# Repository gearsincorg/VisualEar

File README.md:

Visual Ear project
By Phil Malone
Phil.Malone@Mr-Phil.com
6/21/2021

https://hackaday.io/project/175944-the-visual-ear 
 
 This project is an experiment in audio perception.
 My goal was to produce a visual display that might help a deaf person experience sound.
 I got excited when I imagined what an orchestral performance might look like if each musician had such a display above their head.
 
 I started thinking about this project when I discovered that our Cochlea (the sensing part of our inner ear) does not just contain "hairs" that turn vibrations into electrical signals. 
 Instead, it is comprised of many micro structures (containing hairs) which are located along a tapered structure that filters out increasing frequencies of sound as you move into the structure.
 So, in reality, each successive cluster of hairs is detecting higher frequency components. 
 
 Thus the Cochlea does not convert vibrations into electrical impulses, but instead, it converts audio frequencies into electrical impulses.  It's acting as a spectrum analyzer.
 This is a marvelous piece of evolutionary adaption which removed the requirement of the brain to sense signals that were changing many thousands of times a second.
 
 This was quite a revelation to me, and it made me wonder if an external device that converted sound waves into similar frequency bands, and then displayed these bands using light (color and intensity) could be a crude substitute for a Cochlea.

 My first instinct was to think of a spectrum analyzer display that you might see on a high-end audio amplifier.
 There is nothing new about visual audio-spectrum displays, but I decided that it would be important to provide MUCH finer spectral resolution, while still maintaining near real-time response.

Display Specs:

- Display Bands:  104 Bands, spanning 43 Hz - 16744 Hz (8.5 Octaves, 12 LED's per octave)
- Intensity Range: Each Band is displayed with a secific color, and 255 intensity levels
- Display Update interval: 11.6 mSec (86 Hz)
- Audio to Visual Latency:  Max 13.5 mSec (11.6 mSec acquisition + 1.9 mSec for dual FFT & display)
- Visual Persistance:  Low Frequency (< 440 Hz) 185 mSec.  High Frequency (>= 440 Hz) 46 mSec.

 ** HOW IT WORKS 
 
 Note:  Program constants are referenced in this description as follows:  64 (CONSTANT_NAME)
 
 The Teensy audio library is used to sample the I2S digital microphone continuously at the standard 44100 Hz rate.  Successive Bursts of 128 samples are cataloged and saved as an array of Burst pointers.  This array holds 72 (NUM_BURSTS) Burst pointers.  Only 64 (BURSTS_PER_AUDIO) of these are being processed at any time.  The remaining 8 (EXTRA_BURSTS) are used to start capturing more audio while the current Packet of 64 Bursts is processed.  
 
 To cover the full 55-17,153 Hz spectrum, its necessary to aquire 8192 samples (64 Bursts of 128 samples).  But this would take 185 mSec to collect, so its not practical to wait for the full sample to be collected before updating the display.  
 
 To permit faster display updates, a sliding window is created to process the most recent 64 Bursts, every time a new set of 4 (BURSTS_PER_FFT_UPDATE) Bursts have been received.  This event occurs every 11.6 mSec, which becomes the update rate for the overall display (86 updates per second).
 
 A standard FFT (Fast Fourier Transform) is used to convert the Audio Packet (8196 Samples) into frequency buckets.  Initially, a single FFT was used to process the entire sample.  This transform could be performed in the available 11.6 mSec, but a high frequency sound spike would be spread over the entire 185 mS sample duration.  So a sudden sound would appear quickly, but it would persist on the display for the full 185 mSec.  This effectively limits the responsiveness of the system to rapid sounds like a drum roll.
 
 To accommodate BOTH slow low-frequency sounds, and rapid high-frequency sounds, the available Audio packet is processed by two separate FFTs.  Each optimized for a different frequency range.  The Low FFT is looking for sounds in the 55-880 Hz range.   The High FFT is looking for sounds in the 880-17,153 Hz range.  
 
 To capture and resolve low sounds, the Low FFT uses the entire Audio Packet, but it only processes every fourth sample.  This enables the FFT to work with a smaller input sample set of 2048, which still produces 1024 frequency bins of 5.4Hz width.
 
 To capture and resolve rapid high sounds, the High-FFT only uses the most recent quarter of the Audio Packet, but at the full 44.1 kHz sample rate.  This enables this FFT to also work with a smaller input sample set of 2048, but produces 1024 frequency bins of 21.5Hz width.  Since this FFT is only using a quarter of the sample history, short-pulse sounds only persist for a max of 46.4 mSec, which should be able to display a 10 Hz drum-roll.
 
CREDITS:

 > A lot of what I developed here was influenced strongly by Steve Marley https://github.com/s-marley/ESP32_FFT_VU
 
 > An explanation of the Spreadsheet used to determine the Band Bins is found here: https://www.youtube.com/watch?v=Mgh2WblO5_c
 
 > This project adapts the FFT library found here : https://github.com/kosme/arduinoFFT

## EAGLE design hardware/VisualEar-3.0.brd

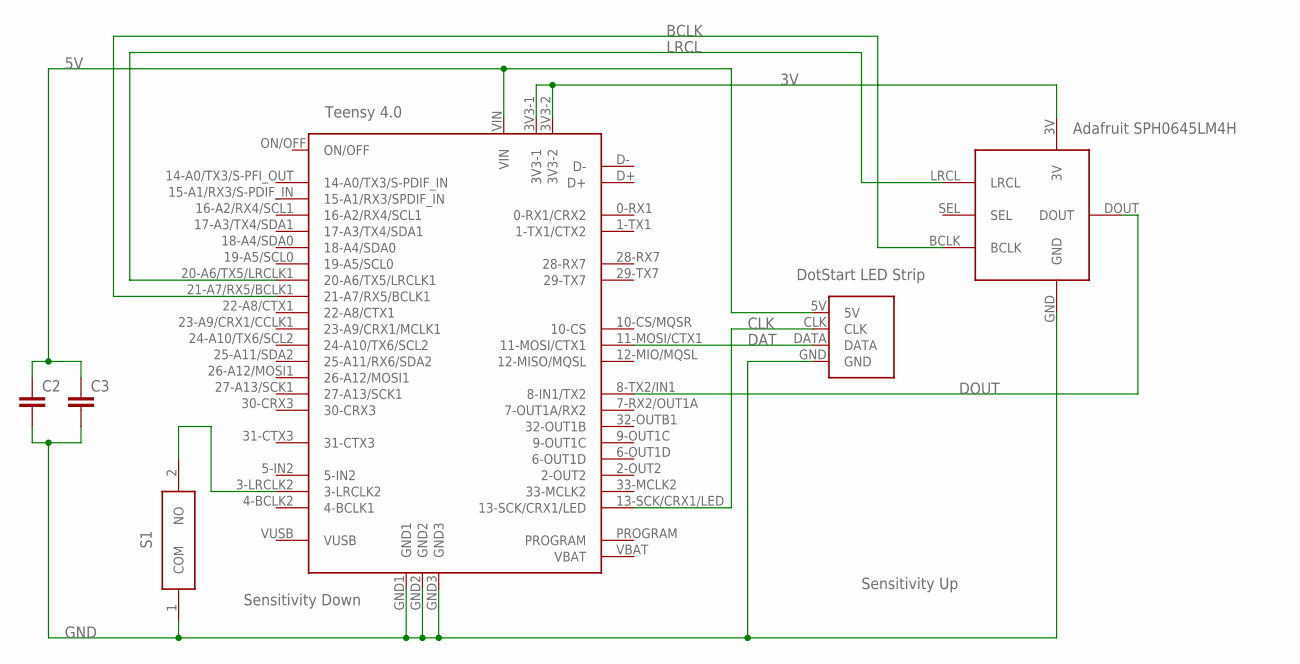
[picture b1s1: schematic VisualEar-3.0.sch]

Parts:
C2, C3: CAPPTH3; CAP-PTH-LARGE
S1: TACTILE-SWITCHTHRU-HOLE; CLICK-WEL
U$1: TEENSY40DIPPLUS5; TEENSY40-DIP+5
U$3: AF-I2S-MIC
U$4: LED-STRIP; LED_STRIP

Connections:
3V: U$1.3V3-1, U$1.3V3-2, U$3.3V
5V: C2.1, C3.1, U$1.VIN, U$4.5V
BCLK: U$1.21-A7/RX5/BCLK1, U$3.BCLK
CLK: U$1.13-SCK/CRX1/LED, U$4.CLK
DAT: U$1.11-MOSI/CTX1, U$4.DATA
DOUT: U$1.8-TX2/IN1 (8-IN1/TX2), U$3.DOUT
GND: C2.2, C3.2, S1.1 (COM), U$1.GND1, U$1.GND2, U$1.GND3, U$3.GND, U$4.GND
LRCL: U$1.20-A6/TX5/LRCLK1, U$3.LRCL
unnamed: S1.2 (NO), U$1.3-LRCLK2

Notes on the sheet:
DotStart LED Strip
Adafruit SPH0645LM4H
Teensy 4.0
Sensitivity Down
Sensitivity Up

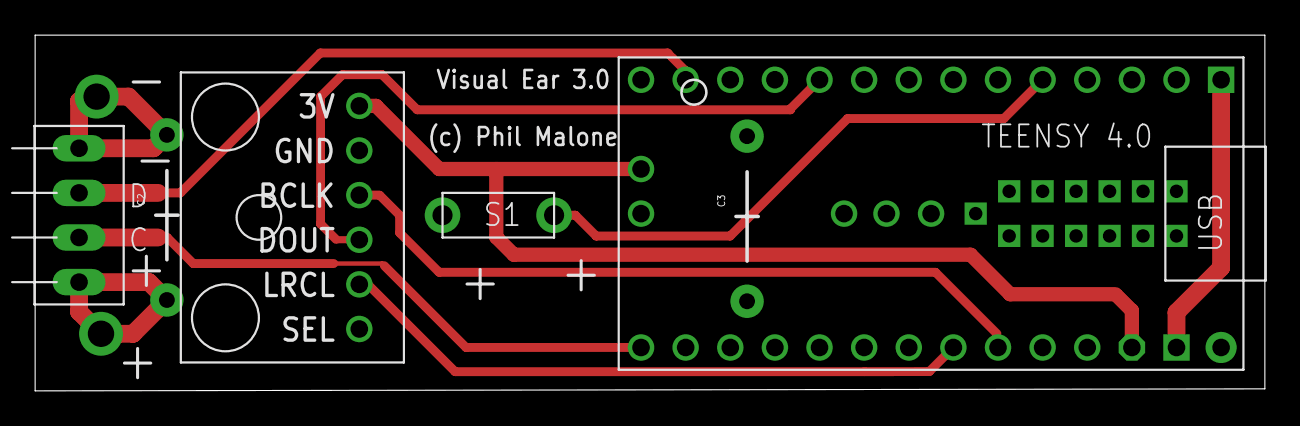
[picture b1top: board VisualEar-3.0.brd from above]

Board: 2 copper layers, 70.0 x 20.2 mm, 6 parts (0 on the bottom side), 9 nets.

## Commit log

2020-12-16 Upgrade to optimal buffering
2021-01-03 Update VisualEar.ino
    Updated header
2021-01-03 Split FFT working
2021-01-16 Added PCB files for Rev 2.0
2021-01-16 Updated to Single Button 3.0 PCB
2021-01-19 REV 3.0 updates
    Reverted back to 59 LEDs .
    Single button gain control.
    Click up, Hold Down
2021-02-08 Added variable sample rate
2021-02-10 104 band release
2021-02-18 Flipped LED order for Inverted display
2021-03-07 Added conf file
2021-03-07 Combined FFT and Balls
2021-03-08 Added AGC
2021-03-09 Move gain controls into Display.h
2021-03-15 Added VU Meter
2021-06-21 Fine tuning
2021-07-12 Adjusted gains lower.
2021-08-12 139 LED tri-band
2021-11-26 137 band update-
2021-11-26 Changed to 104 bands (12 bands per octave)
2022-01-18 Added new pitch Mode
2022-02-02 Release 2.0
    First 4 function release
2022-10-27 First test
2022-12-20 Final Release code
2022-12-20 New Files
2022-12-22 First Functional
2022-12-22 Working Anti-Alias Filter
2022-12-26 Fully functional
2022-12-30 Added Version Info to Serial
2022-12-30 Added Revision Info to Serial
2023-04-27 Named the modes
2023-04-28 Updated Start Text
2025-06-02 Added ocean/bubble mode
